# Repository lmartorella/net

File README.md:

# Home

This is a hobbist/educational fulls stack project about Internet of Things (IoT) for DIY enthusiasts. It starts from scratch, using bare microcontrollers (MCU), network, and PC software without any relevant dependency.

The idea is about implementing a lost-cost open-source, open-hardware wired platform for general purpose automation control (for example domotic projects, security, garden automation, etc...). It is designed to connect a whole home and its surroundings.

The core of the project is a tiny MCU board that can embedded in any hardware, even a normal wall switch.

Node-to-node communication happens via common 4-wire or 6-wire low-voltage cables, like KNX, CAN-bus or other commercial systems, using industrial-grade [RS-485](https://en.wikipedia.org/wiki/RS-485) specifications for great scalability. Node-to-master communication is through IP (e.g. ethernet, wifi, etc...) for improved scalability. This allow wireless nodes to be implemented as well. 

What this project is aimed to:
- connect any type of sensor 
- integrate devices that can be interfaced via a MCU
- log data
- implement custom logic to automate tasks
- have a web interface for remote control

The bus structure allow extension with other open standards for IoT.

# The network

The network topology uses two mediums: a custom wired low-voltage bus to allow simple MCUs to be used, and a higher LAN/IP level to aggregate wired sections and server connection.

The wired design is similar to the [KNX](https://en.wikipedia.org/wiki/KNX_(standard)) open standard. However, instead of using proprietary electrical bus drivers, it relies on the broadly available [RS-485](https://en.wikipedia.org/wiki/RS-485) standard (for example, a [Maxim MAX485 IC](https://www.maximintegrated.com/en/products/interface/transceivers/MAX485.html) can be used as a driver).

An industrial-level RS-485 bus can range up to 32 nodes on the same wire and span hundreds of meters, even on electrically noisy environments. See [Maxim Integrated AN](https://www.maximintegrated.com/en/app-notes/index.mvp/id/3884).

Frames are byte-oriented, allowing a common bi-directional [UART](https://en.wikipedia.org/wiki/Universal_asynchronous_receiver-transmitter) to be used. This simplifies the selection of the hardware, since no bit-level CAN-bus or MODBUS logic is required. 

Each wired section needs to contain a *master* node, that allows IP connection to the server through Wi-Fi or Ethernet cables (it needs both UDP and TCP).

The custom protocol built on top is designed to offer features to ease the network installation:
- Auto-discovery for all connected nodes
- Zero-configuration: allow dynamic allocation of nodes via push-button and a PC application
- Fail-over due to bus failures, IP connection failures or node failures.

The byte-level message-based protocol is then shared between wired sections and to increase simplicity and issue analysis.

More details [in this page](doc/protocol.md).

# The microbean (µBean)

The prototyped hardware is a small board (just 30x28mm) built around a cost-effective [Microchip PIC16F1827 MCU](https://www.microchip.com/wwwproducts/en/PIC16F1827), a RS-485 level adapter and a voltage regulator. The board expose almost all MCU lines to the maker, allowing a great amount of free digital and analog I/O pins.

Once the MCU are programmed, the network topology can be easily configured with a PC.

Each physical node exposes one or more applicative drivers, called *sinks*. In this way, a single bean can be programmed to interface more than one device.

More details can be found [here](./src/nodes/doc/microbean.md).

# Some examples

A collection of sample code for beans can be found in the samples folder.

Each sample is documented [here](./samples/beans/README.md).

## Light control

One bean installed in each wall box.
- Common switches will be used as low power digital switch drivers, or push button style
- Touch switches support
- RGB LEDs can be installed in each switch allowing soft tone transitions and night mode
- Power line relays or FET boards in separated junction boxes to control lights
- PWM with zero-cross detection dimmer boards for bulbs that support it
- IR motion/presence sensors support
- Luminance sensors for power saving support

## Intrusion detection and report

- A bean for each IR/motion sensor.
- A bean in junction boxes for window and doors magnetic switch.
- Beans at entrances for RFID or physical keys.
- Real-time notification of unusual activity
- Phone call/SMS/IM alert
- Remote control
- Remote activation/deactivation
- Smartphone control

## Climatization

Beans can be used to interact with existing climatization systems
- Temperature and humidity sensors
- IR emitters for fans and air conditioning units
- Actuator interfacing for motorized window shutters
- Regulation made based on weather forecast services

## Garden irrigation system

- Beans to control electrical valves
- Rain sensors
- Level meter for water tanks
- Relays board for submerged pumps
- Planning made based on weather forecast services

## Power management

- Interfacing with power meters that supports a serial port or a IP protocol.
- Interfacing with solar inverters.
- Wind meters to auto-close awnings.
- Connection with smart meters and devices.

# How to build

The project contains software elements (the .NET server, the node simulators and the control panel UI), hardware (the microbean) and the firmware for these nodes.

It is however possible to run the system with a software-only environment, using the node simulators to have a try.

## The server

The server code is a C# command-line process. It doesn't have any 3rd party dependency other than the .NET Framework, and it could be easily ported to [.NET Core](https://dotnet.microsoft.com/download).

However, currently it requires [Visual Studio](https://visualstudio.microsoft.com/) and [.NET Framework 4.x](https://dotnet.microsoft.com/download).

The project is splitted between the core part and the samples dlls, that are loaded automatically at startup via a plug-in load system, allowing modular architecture.

In addition, a WPF application is generated as a administrative interface (to visualize and set-up the network hierarchy) and to allow simulation of node logic and his sinks.

See [here](src/server/README.md) for more information.

## The master node

A master node is required to translate the IP connection from the server to the wired sections.

Custom hardware can be used there, but the simplest solution is perhaps to use an Arduino or a [Raspberry Pi Zero W](https://www.raspberrypi.org/products/raspberry-pi-zero-w/): something that can drive a bidirectional serial port and that can be connected to the LAN.

In this project you will found two implementations:
- for Raspberry (Raspbian) 
- for Microchip MCU with Ethernet support (e.g. PIC18F87). The [Microchip MPLAB X IDE](https://www.microchip.com/mplab/mplab-x-ide) with [XC8 compiler](https://www.microchip.com/mplab/compilers) is required in this case.

See [here](src/nodes/README.md) for more information.

## The wired node

You will find the schematics and the Microchip firmware to implement a wired node. Different ranges of MCU can be used, since the code and data requirements are quite limited.

The [Microchip MPLAB X IDE](https://www.microchip.com/mplab/mplab-x-ide) with [XC8 compiler](https://www.microchip.com/mplab/compilers) is required to compile the firmware and the samples.

See [here](src/nodes/README.md) for more information.

## The web server

A minimalistic web-server implementation is presented to allow remote access to the applications exposed by the server.

See [here](src/web/README.md) for more information.

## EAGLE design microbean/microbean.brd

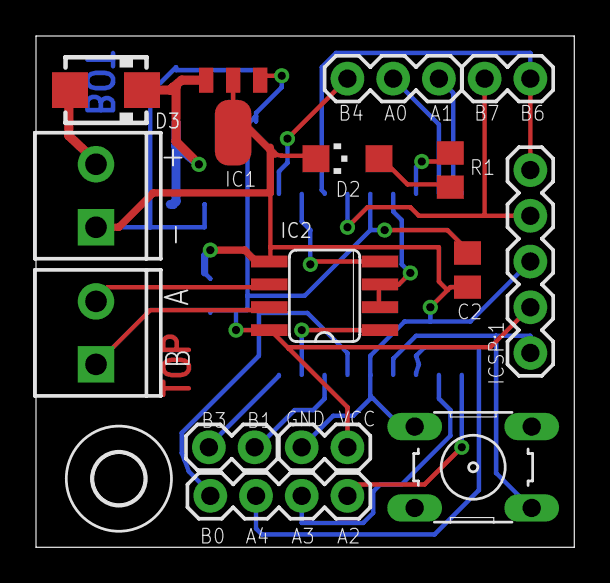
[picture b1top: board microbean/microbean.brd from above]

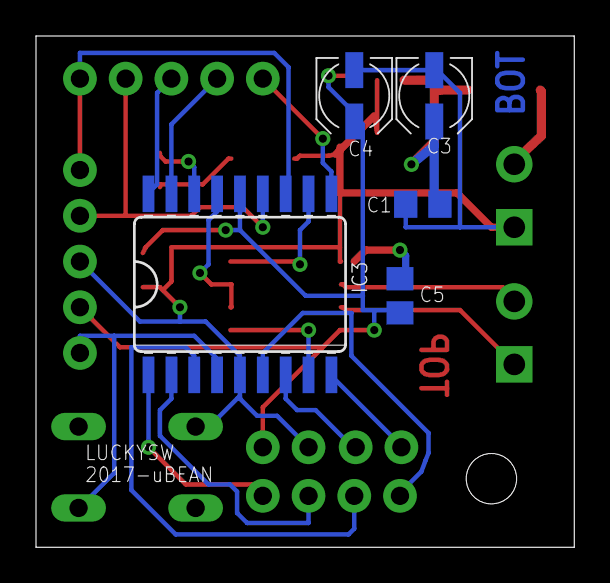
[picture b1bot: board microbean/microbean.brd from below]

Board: 2 copper layers, 29.9 x 28.4 mm, 21 parts (5 on the bottom side), 23 nets.

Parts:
C1, C2, C5: 100n; C0805
C3, C4: 10u; UD-4X5,8_NICHICON
D2: LED1206; CHIPLED_1206
D3: S1A; SMA
IC1: L78L33/L78L05; SOT89
IC2: ST485/ST3485; SO08
IC3: PIC16F1827SO18; SO18W
ICSP: ICSP-HEADER-5; 1X05
J1, J2: SCREWTERMINAL-3.5MM-2
J3: 1X03
J4: 1X04
J5, J6, J7: 1X02
R1: 560; R0805
U$2: PUSH-BUTTON; MICRO-SWITCH
U$4: 2,8

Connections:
A: IC2.6, J2.2
B: IC2.7, J2.1
GND: C1.2, C2.2, C3.-, C4.-, C5.2, D2.C, IC1.2, IC1.2@1, IC2.5, IC3.5, ICSP.3, J1.1, J5.2, U$2.1
MCLR: IC3.4, ICSP.1, U$2.4
unnamed: D3.A, J1.2
unnamed: C1.1, C3.+, D3.C, IC1.3
unnamed: D2.A, R1.2
RA0: IC3.17, J3.2
RA1: IC3.18, J3.3
RA2: IC3.1, J4.1
RA3: IC3.2, J4.2
RA4: IC3.3, J4.3
RA6: IC2.2, IC2.3, IC3.15
RA7: IC3.16, R1.1
RB0: IC3.6, J4.4
RB1: IC3.7, J7.2
RB2: IC2.1, IC3.8
RB3: IC3.9, J7.1
RB4: IC3.10, J3.1
RB5: IC2.4, IC3.11
RB6: IC3.12, ICSP.5, J6.2
RB7: IC3.13, ICSP.4, J6.1
VCC: C2.1, C4.+, C5.1, IC1.1, IC2.8, IC3.14, ICSP.2, J5.1

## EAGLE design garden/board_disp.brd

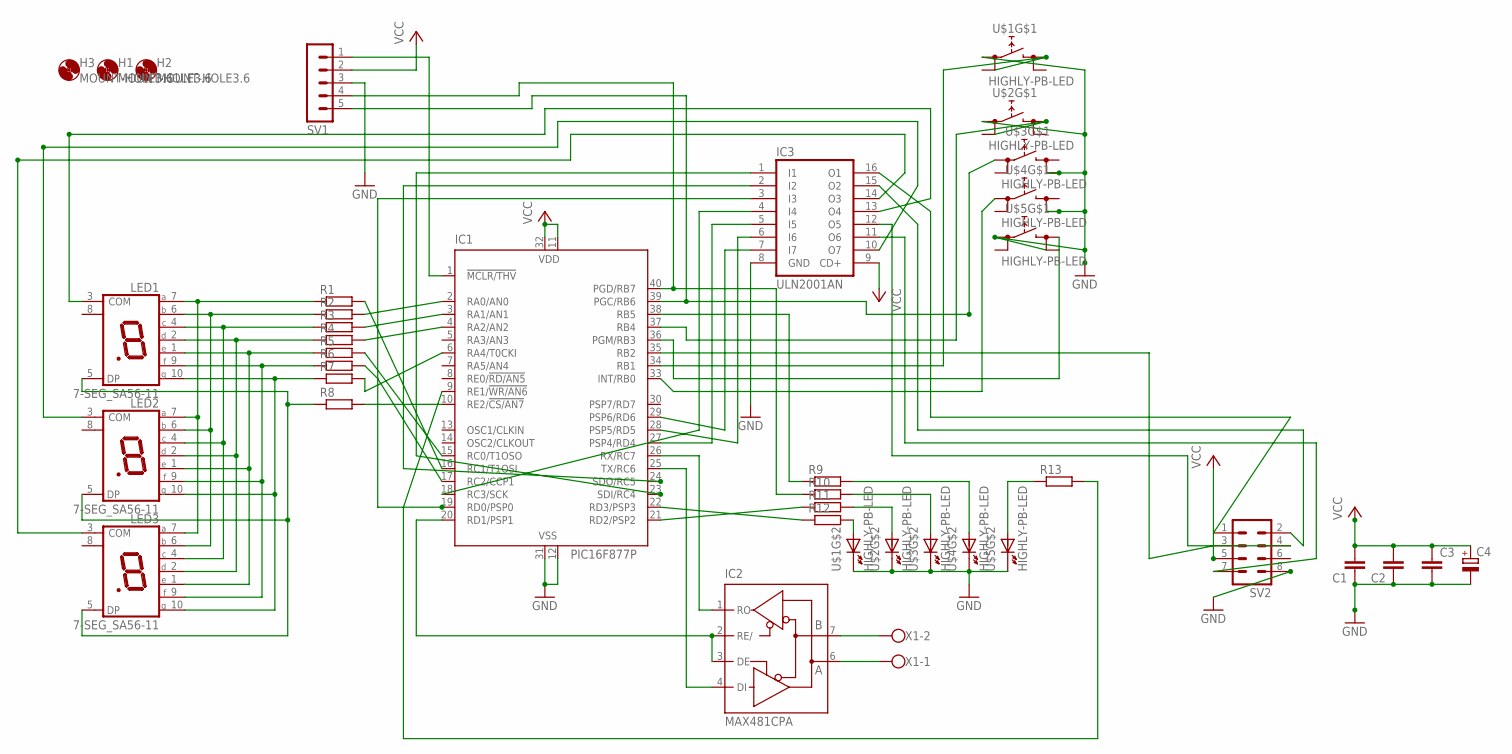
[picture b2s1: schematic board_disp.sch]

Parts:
C1, C2, C3: C-EU025_050-025X075; C025_050-025X075
C4: CPOL-EUE3.5-8; E3,5-8
H1, H2, H3: MOUNT-HOLE3.6; 3,6
IC1: PIC16F877P; DIL40
IC2: MAX481CPA; DIL08
IC3: ULN2001AN; DIL16
LED1, LED2, LED3: 7-SEG_SA56-11; SA56-11
R1, R2, R3, R4, R5, R6, R7, R8, R9, R10, R11, R12, R13: R-EU_0207/10; 0207/10
SV1: MA05-1
SV2: MA04-2
U$1, U$2, U$3, U$4, U$5: HIGHLY-PB-LED; HIGHLY-PUSHBUTTON
X1: PASSO3

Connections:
GND: C1.1, C2.1, C3.2, C4.-, IC1.12 (VSS), IC1.31 (VSS), IC2.5 (GND), IC3.8 (GND), SV1.3, SV2.8, U$1.1A (0), U$1.K, U$2.1A (0), U$2.K, U$3.2B (1), U$3.K, U$4.2B (1), U$4.K, U$5.1A (0), U$5.K
unnamed: IC1.36 (PGM/RB3), U$5.2A (1)
unnamed: IC1.33 (INT/RB0), U$4.1A (0)
unnamed: IC1.39 (PGC/RB6), SV1.5, U$3.1A (0)
unnamed: IC1.37 (RB4), U$2.2A (1)
unnamed: IC1.34 (RB1), U$1.2A (1)
unnamed: IC1.6 (RA4/T0CKI), R7.2
unnamed: LED1.5 (DP), LED2.5 (DP), LED3.5 (DP), R8.1
unnamed: IC1.10 (RE2/!CS/AN7), R8.2
unnamed: IC1.22 (RD3/PSP3), R12.1
unnamed: R12.2, U$1.A
unnamed: R11.2, U$2.A
unnamed: R10.2, U$3.A
unnamed: R9.2, U$4.A
unnamed: IC1.16 (RC1/T1OSI), R1.2
unnamed: LED1.7 (A), LED2.7 (A), LED3.7 (A), R1.1
unnamed: LED1.6 (B), LED2.6 (B), LED3.6 (B), R2.1
unnamed: LED1.4 (C), LED2.4 (C), LED3.4 (C), R3.1
unnamed: LED1.2 (D), LED2.2 (D), LED3.2 (D), R4.1
unnamed: LED1.1 (E), LED2.1 (E), LED3.1 (E), R5.1
unnamed: LED1.9 (F), LED2.9 (F), LED3.9 (F), R6.1
unnamed: LED1.10 (G), LED2.10 (G), LED3.10 (G), R7.1
unnamed: IC1.21 (RD2/PSP2), R11.1
unnamed: IC1.18 (RC3/SCK), IC3.4 (I4)
unnamed: IC1.27 (PSP4/RD4), IC3.5 (I5)
unnamed: IC1.17 (RC2/CCP1), R6.2
unnamed: IC1.15 (RC0/T1OSO), R5.2
unnamed: IC1.4 (RA2/AN2), R4.2
unnamed: IC1.3 (RA1/AN1), R3.2
unnamed: IC1.2 (RA0/AN0), R2.2
unnamed: IC1.38 (RB5), R9.1
unnamed: IC2.7 (B), X1.2
unnamed: IC2.6 (A), X1.1
unnamed: IC1.23 (SDI/RC4), IC3.1 (I1)
unnamed: IC1.24 (SDO/RC5), IC3.2 (I2)
unnamed: IC1.19 (RD0/PSP0), IC3.3 (I3)
unnamed: IC3.13 (O4), LED1.3 (COM)
unnamed: IC3.10 (O7), LED2.3 (COM)
unnamed: IC3.14 (O3), LED3.3 (COM)
unnamed: IC1.35 (RB2), SV2.3
unnamed: IC1.29 (PSP6/RD6), IC3.7 (I7)
unnamed: IC1.28 (PSP5/RD5), IC3.6 (I6)
unnamed: IC1.26 (RX/RC7), IC2.1 (RO)
unnamed: IC1.25 (TX/RC6), IC2.4 (DI)
unnamed: IC1.20 (RD1/PSP1), IC2.2 (RE/), IC2.3 (DE)
unnamed: IC1.40 (PGD/RB7), R10.1, SV1.4
unnamed: IC1.1 (!MCLR/THV), SV1.1
unnamed: IC3.16 (O1), SV2.1
unnamed: IC3.15 (O2), SV2.2
unnamed: IC3.11 (O6), SV2.7
unnamed: IC3.12 (O5), SV2.4
unnamed: R13.1, U$5.A
unnamed: IC1.9 (RE1/!WR/AN6), R13.2
VCC: C1.2, C2.2, C3.1, C4.+, IC1.11 (VDD), IC1.32 (VDD), IC2.8 (VCC), IC3.9 (CD+), SV1.2, SV2.5

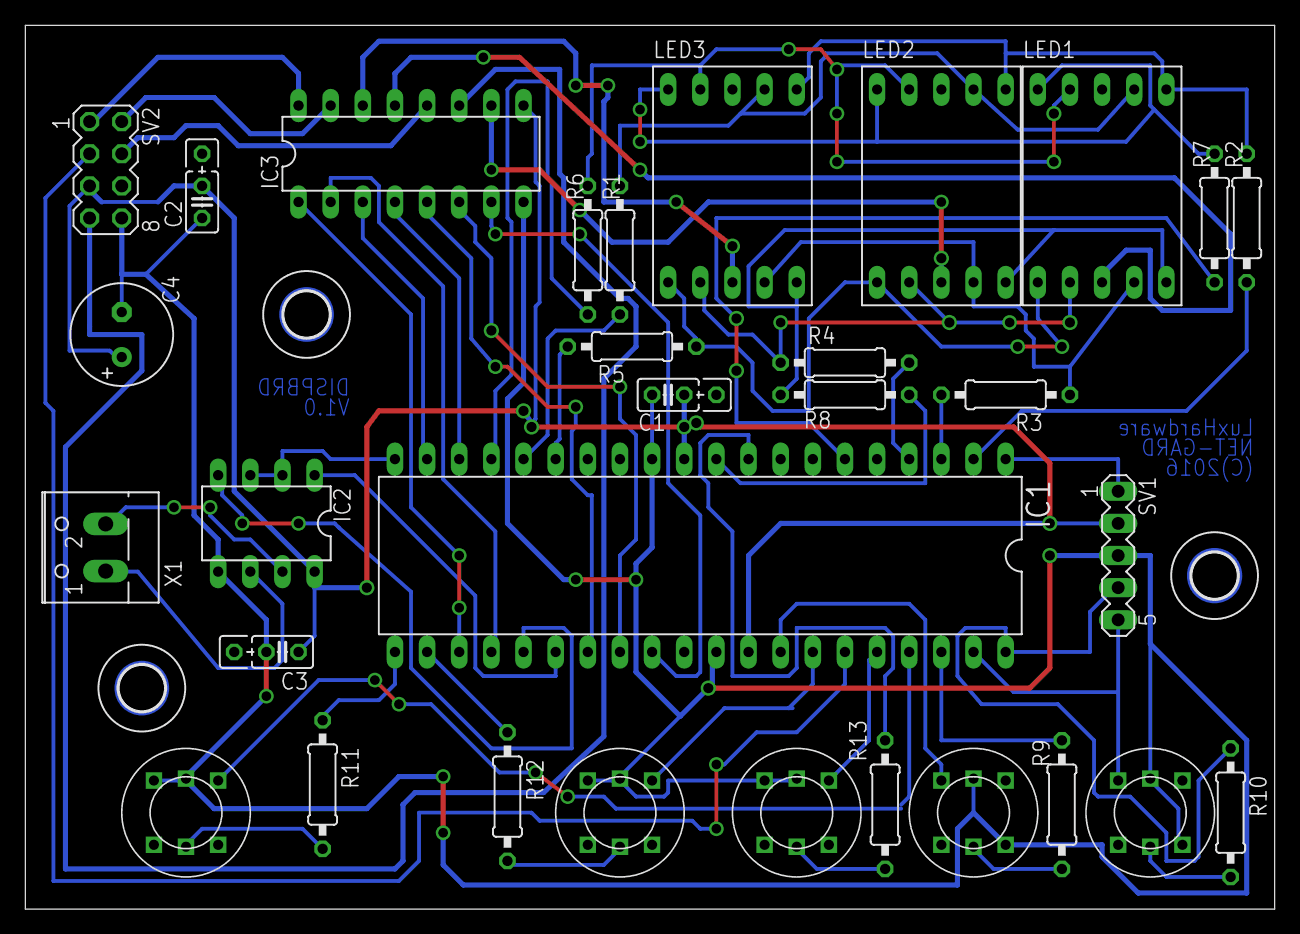
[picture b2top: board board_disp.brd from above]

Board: 2 copper layers, 98.7 x 69.8 mm, 34 parts (0 on the bottom side), 54 nets.

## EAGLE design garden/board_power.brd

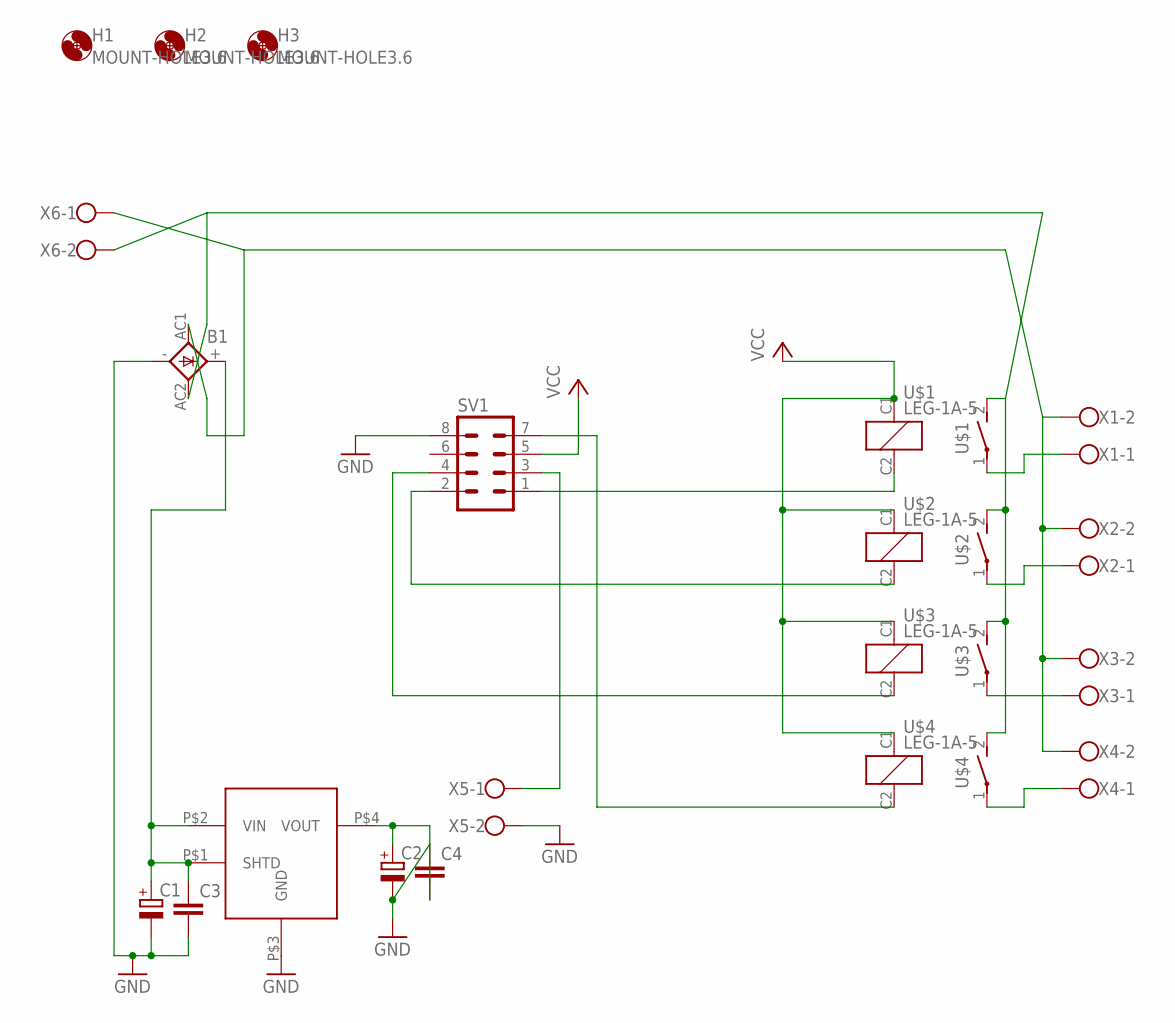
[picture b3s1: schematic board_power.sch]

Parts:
B1: KBK10A
C1, C2: CPOL-EUE5-4; E5-4
C3, C4: C-EU025_050-025X075; C025_050-025X075
H1, H2, H3: MOUNT-HOLE3.6; 3,6
SV1: MA04-2
U$1, U$2, U$3, U$4: LEG-1A-5; LEG
U$5: POLOLU-2098
X1, X2, X3, X4, X5, X6: PASSO3

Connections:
GND: B1.-, C1.-, C2.-, C3.2, C4.1, SV1.8, U$5.P$3 (GND), X5.2
unnamed: SV1.1, U$1.C2 (2)
unnamed: SV1.2, U$2.C2 (2)
unnamed: SV1.4, U$3.C2 (2)
unnamed: SV1.7, U$4.C2 (2)
unnamed: SV1.3, X5.1
unnamed: B1.AC2, U$1.2 (S), U$2.2 (S), U$3.2 (S), U$4.2 (S), X6.2
unnamed: B1.AC1, X1.2, X2.2, X3.2, X4.2, X6.1
unnamed: U$1.1, X1.1
unnamed: U$2.1, X2.1
unnamed: U$3.1, X3.1
unnamed: U$4.1, X4.1
unnamed: B1.+, C1.+, C3.1, U$5.P$1 (SHTD), U$5.P$2 (VIN)
unnamed: C2.+, C4.2, U$5.P$4 (VOUT)
VCC: SV1.5, U$1.C1 (1), U$2.C1 (1), U$3.C1 (1), U$4.C1 (1)

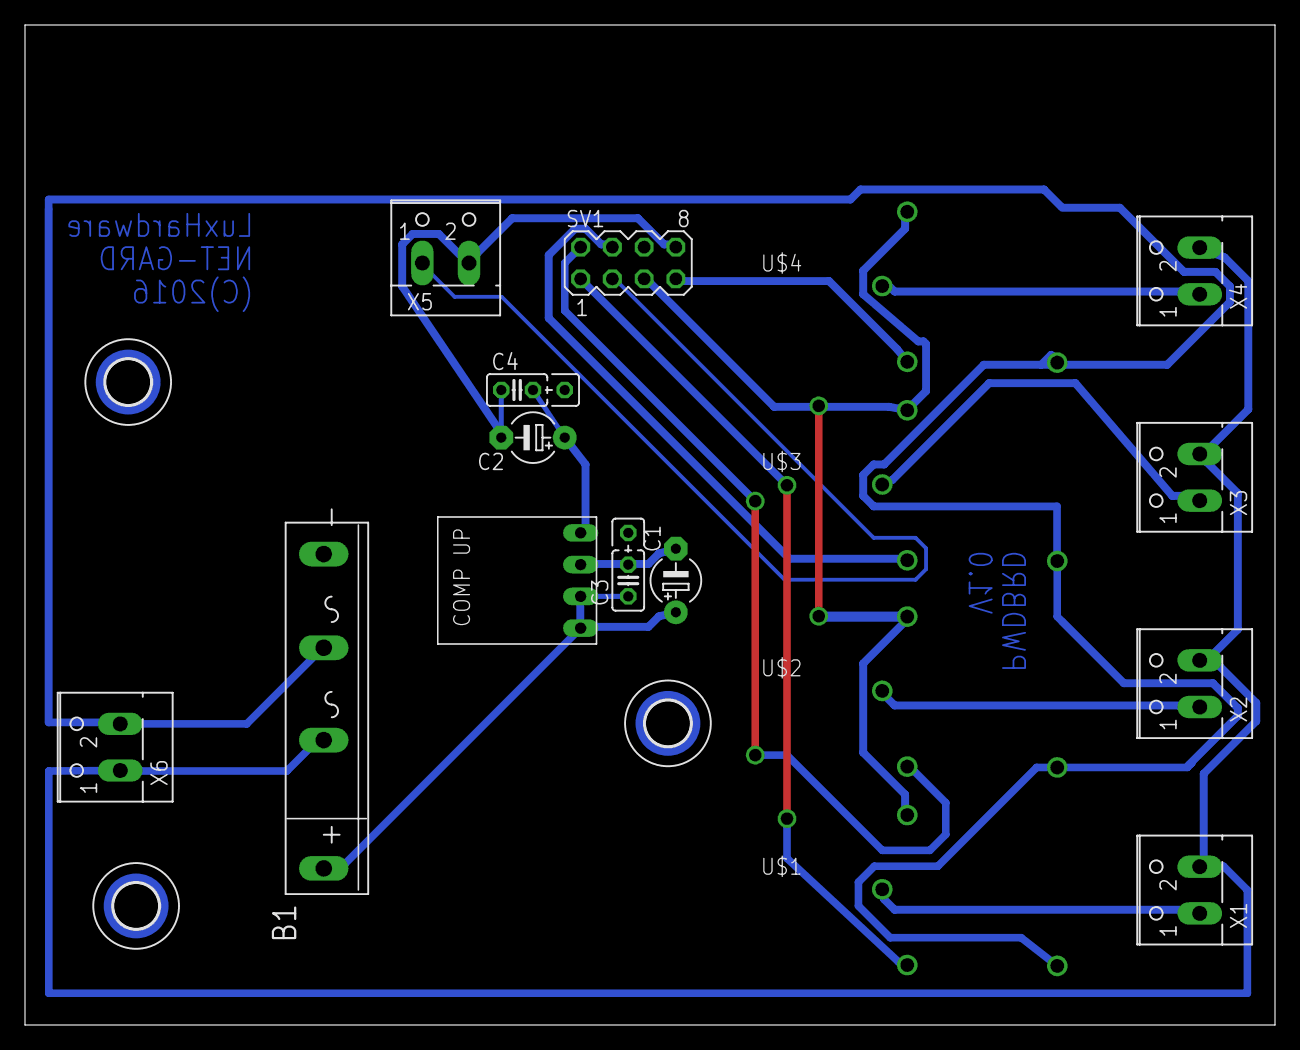
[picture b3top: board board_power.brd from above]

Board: 2 copper layers, 100.0 x 80.0 mm, 20 parts (0 on the bottom side), 15 nets.

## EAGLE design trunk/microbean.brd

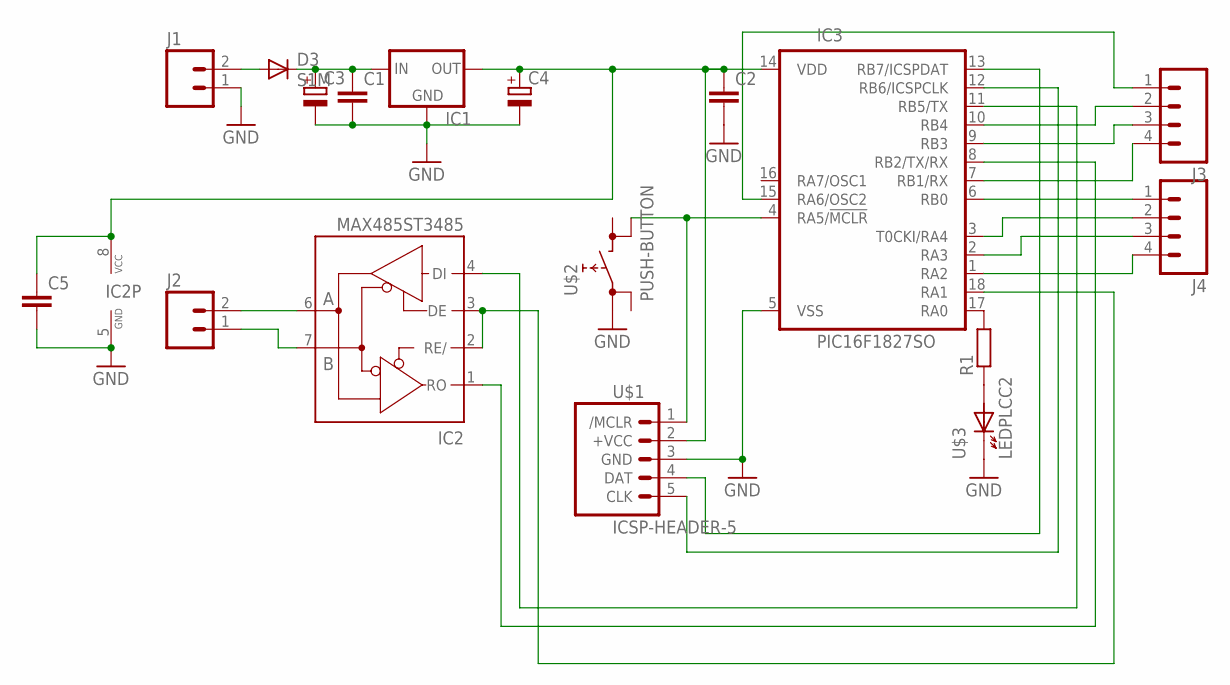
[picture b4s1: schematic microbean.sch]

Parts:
C1, C2, C5: C-EUC0805; C0805
C3, C4: CPOL-EUE2-4; E2-4
D3: S1M; SMA
IC1: 78LXXSOT89; SOT89
IC2: MAX485ST3485; SO08
IC3: PIC16F1827SO; SO-18W
J1, J2: M02-SCREW-3.5MM3.5MM; SCREWTERMINAL-3.5MM-2
J3, J4: M04; 1X04
R1: R-EU_R0805; R0805
U$1: ICSP-HEADER-5; 1X05
U$2: PUSH-BUTTON; MICRO-SWITCH
U$3: LEDPLCC2; P-LCC-2

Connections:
GND: C1.2, C2.2, C3.-, C4.-, C5.2, IC1.2 (GND), IC2.5 (GND), IC3.5 (VSS), J1.1, U$1.3 (GND), U$2.1 (0), U$3.C (K)
unnamed: D3.A, J1.2
unnamed: C1.1, C3.+, D3.C, IC1.3 (IN)
unnamed: IC2.7 (B), J2.1
unnamed: IC2.6 (A), J2.2
unnamed: IC3.4 (RA5/!MCLR), U$1.1 (/MCLR), U$2.4 (1)
unnamed: IC3.13 (RB7/ICSPDAT), U$1.4 (DAT)
unnamed: IC3.12 (RB6/ICSPCLK), U$1.5 (CLK)
unnamed: IC3.17 (RA0), R1.2
unnamed: R1.1, U$3.A
unnamed: IC2.4 (DI), IC3.11 (RB5/TX)
unnamed: IC2.1 (RO), IC3.8 (RB2/TX/RX)
unnamed: C2.1, C4.+, C5.1, IC1.1 (OUT), IC2.8 (VCC), IC3.14 (VDD), U$1.2 (+VCC)
unnamed: IC3.1 (RA2), J4.4
unnamed: IC3.2 (RA3), J4.3
unnamed: IC3.3 (T0CKI/RA4), J4.2
unnamed: IC3.6 (RB0), J4.1
unnamed: IC3.7 (RB1/RX), J3.4
unnamed: IC3.9 (RB3), J3.3
unnamed: IC3.10 (RB4), J3.2
unnamed: IC3.15 (RA6/OSC2), J3.1
unnamed: IC2.2 (RE/), IC2.3 (DE), IC3.18 (RA1)

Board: 2 copper layers, 17 parts (1 on the bottom side), 22 nets, no tracks yet.

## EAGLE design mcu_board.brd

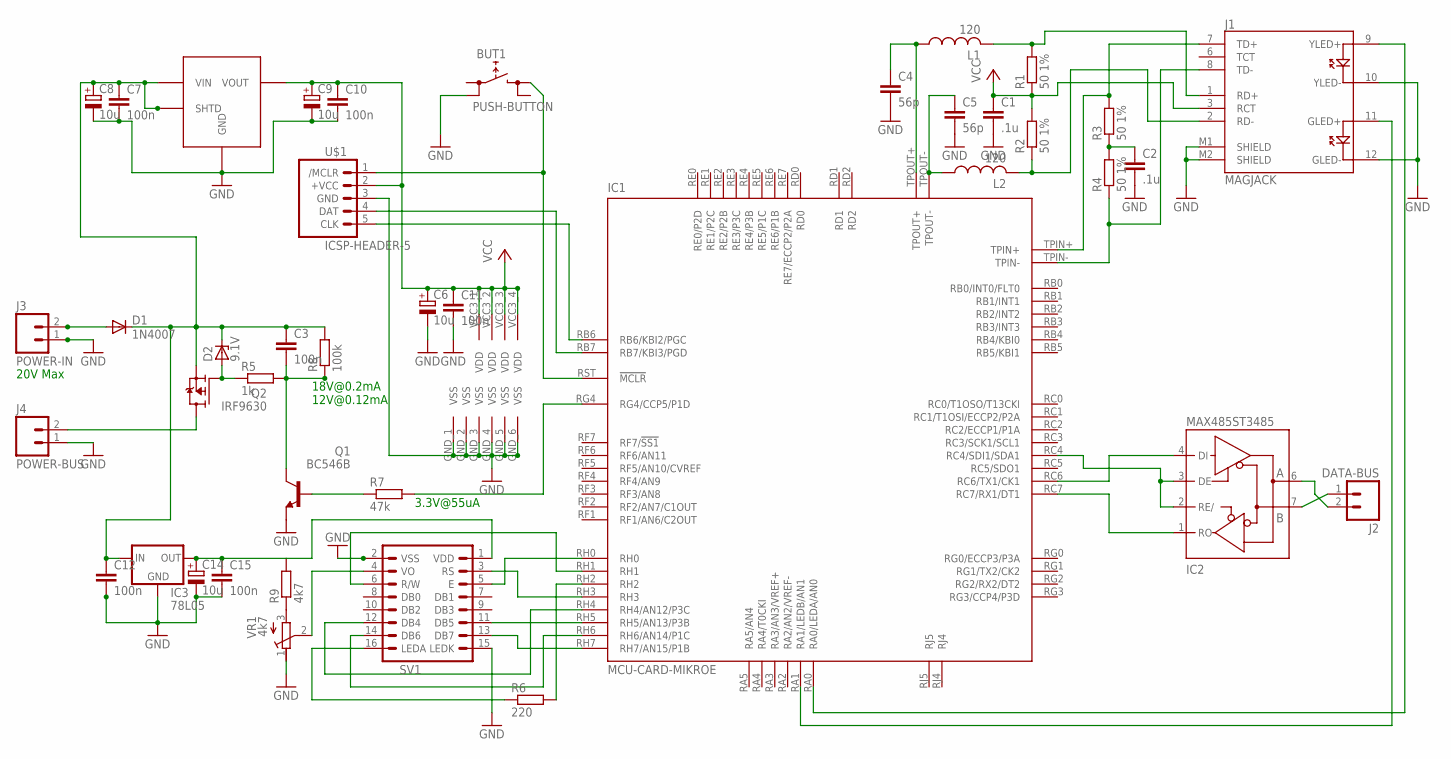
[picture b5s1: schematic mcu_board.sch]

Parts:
BUT1: PUSH-BUTTON; MICRO-SWITCH
C1, C2: .1u; C050-025X075
C3, C7, C10, C11, C12, C15: 100n; C050-025X075
C4, C5: 56p; C0805
C6: 10u; E2,5-6
C8, C9, C14: 10u; E2,5-7
D1: 1N4007; DO41-10
D2: 9.1V; D-5
IC1: MCU-CARD-MIKROE; LV18F
IC2: MAX485ST3485; SO08
IC3: 78L05; 78LXX
J1: MAGJACK
J2: DATA-BUS; SCREWTERMINAL-3.5MM-2
J3: POWER-IN; SCREWTERMINAL-3.5MM-2
J4: POWER-BUS; SCREWTERMINAL-3.5MM-2
L1, L2: 120; R0603
Q1: BC546B; TO92-
Q2: IRF9630; TO220V
R1, R2, R3, R4: 50 1%; 0207/10
R5: 1k; 0207/10
R6: 220; 0207/10
R7: 47k; 0207/10
R8: 100k; 0207/10
R9: 4k7; 0207/10
SV1: WM-C2002M-DISP; MA08-2
U$1: ICSP-HEADER-5; 1X05
U$3: POLOLU-2098; POLOLU-10-13
VR1: 4k7; V_TRIMMER

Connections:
GND: BUT1.2 (0), C1.2, C2.2, C4.2, C5.2, C6.-, C7.2, C8.-, C9.-, C10.2, C11.2, C12.2, C14.-, C15.2, IC1.GND_1 (VSS), IC1.GND_2 (VSS), IC1.GND_3 (VSS), IC1.GND_4 (VSS), IC1.GND_5 (VSS), IC1.GND_6 (VSS), IC2.5 (GND), IC3.GND, J1.10 (YLED-), J1.12 (GLED-), J1.M1 (SHIELD), J1.M2 (SHIELD), J3.1, J4.1, Q1.1 (E), SV1.2 (VSS), SV1.15 (LEDK), U$1.3 (GND), U$3.P$3 (GND), VR1.1 (A)
unnamed: C4.1, IC1.TPOUT+, L1.1
unnamed: C2.1, R3.1, R4.2
unnamed: J1.1 (RD+), L1.2, R1.2
unnamed: J1.2 (RD-), L2.2, R2.1
unnamed: IC1.TPIN+, J1.7 (TD+), R3.2
unnamed: IC1.TPIN-, J1.8 (TD-), R4.1
unnamed: C5.1, IC1.TPOUT-, L2.1
unnamed: IC1.RC7 (RC7/RX1/DT1), IC2.1 (RO)
unnamed: IC1.RA0 (RA0/LEDA/AN0), J1.9 (YLED+)
unnamed: IC1.RA1 (RA1/LEDB/AN1), J1.11 (GLED+)
unnamed: IC1.RC6 (RC6/TX1/CK1), IC2.4 (DI)
unnamed: IC1.RC4 (RC4/SDI1/SDA1), IC2.2 (RE/), IC2.3 (DE)
unnamed: BUT1.3 (1), IC1.RST (!MCLR), U$1.1 (/MCLR)
unnamed: IC1.RB6 (RB6/KBI2/PGC), U$1.5 (CLK)
unnamed: IC1.RB7 (RB7/KBI3/PGD), U$1.4 (DAT)
unnamed: IC1.RH0, SV1.5 (E)
unnamed: IC1.RH1, SV1.6 (R/W)
unnamed: IC2.7 (B), J2.1
unnamed: IC1.RH3, SV1.3 (RS)
unnamed: IC1.RH4 (RH4/AN12/P3C), SV1.12 (DB4)
unnamed: IC1.RH5 (RH5/AN13/P3B), SV1.11 (DB5)
unnamed: IC1.RH6 (RH6/AN14/P1C), SV1.14 (DB6)
unnamed: IC1.RH7 (RH7/AN15/P1B), SV1.13 (DB7)
unnamed: IC2.6 (A), J2.2
unnamed: D1.A, J3.2
unnamed: SV1.4 (VO), VR1.2 (S)
unnamed: J4.2, Q2.2 (D)
unnamed: IC1.RG4 (RG4/CCP5/P1D), R7.2
unnamed: D2.A, Q2.1 (G), R5.1
unnamed: R6.1, SV1.16 (LEDA)
unnamed: IC1.RH2, R6.2
unnamed: C3.2, Q1.3 (C), R5.2, R8.1
unnamed: Q1.2 (B), R7.1
unnamed: R9.1, VR1.3 (E)
VCC: C1.1, C6.+, C9.+, C10.1, C11.1, IC1.VCC3_1 (VDD), IC1.VCC3_2 (VDD), IC1.VCC3_3 (VDD), IC1.VCC3_4 (VDD), IC2.8 (VCC), J1.3 (RCT), R1.1, R2.2, U$1.2 (+VCC), U$3.P$4 (VOUT)
VCC5: C14.+, C15.1, IC3.OUT, R9.2, SV1.1 (VDD)
VIN: C3.1, C7.1, C8.+, C12.1, D1.C, D2.C, IC3.IN, Q2.3 (S), R8.2, U$3.P$1 (SHTD), U$3.P$2 (VIN)

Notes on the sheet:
18V@0.2mA 12V@0.12mA
3.3V@55uA
20V Max

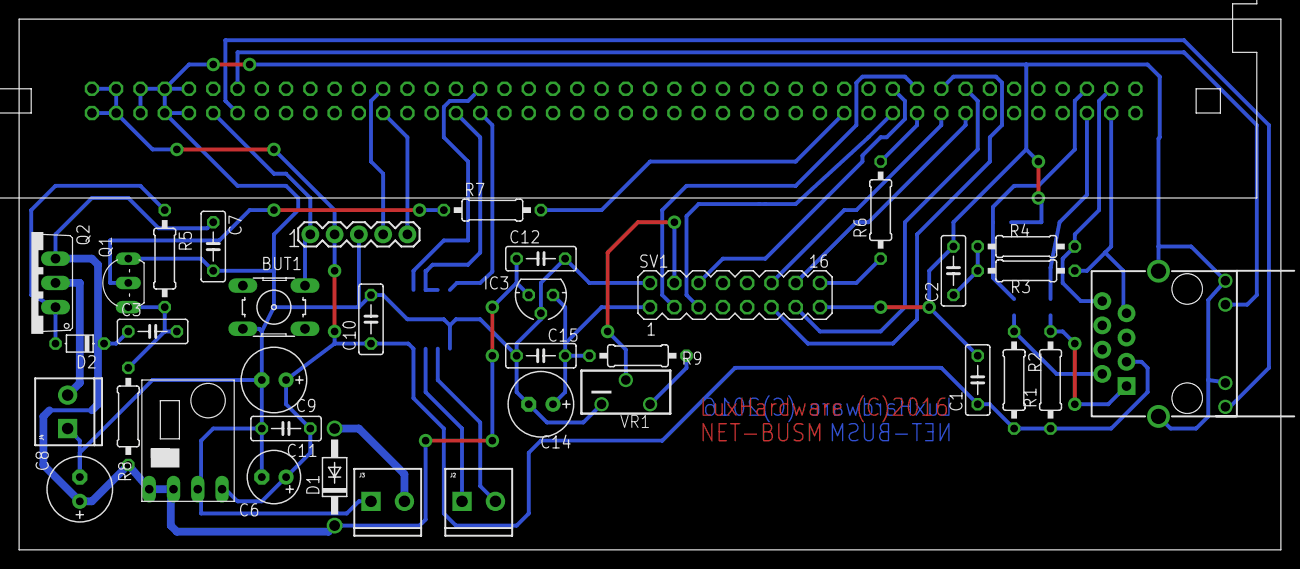
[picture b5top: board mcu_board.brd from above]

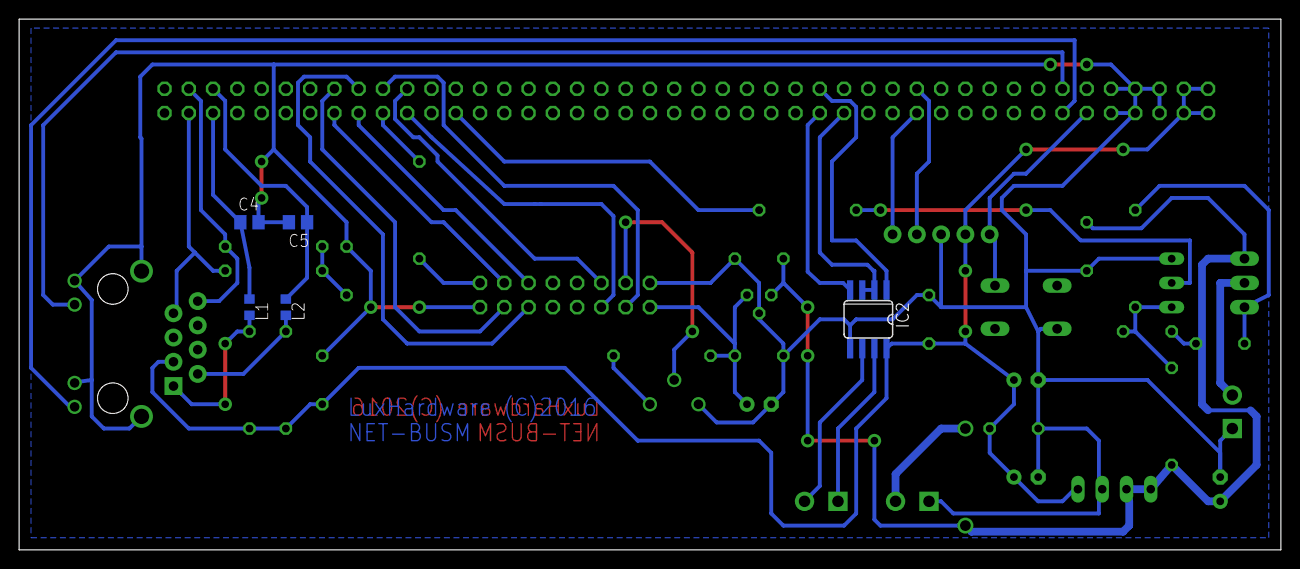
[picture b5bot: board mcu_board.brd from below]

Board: 2 copper layers, 132.1 x 55.5 mm, 41 parts (5 on the bottom side), 38 nets.

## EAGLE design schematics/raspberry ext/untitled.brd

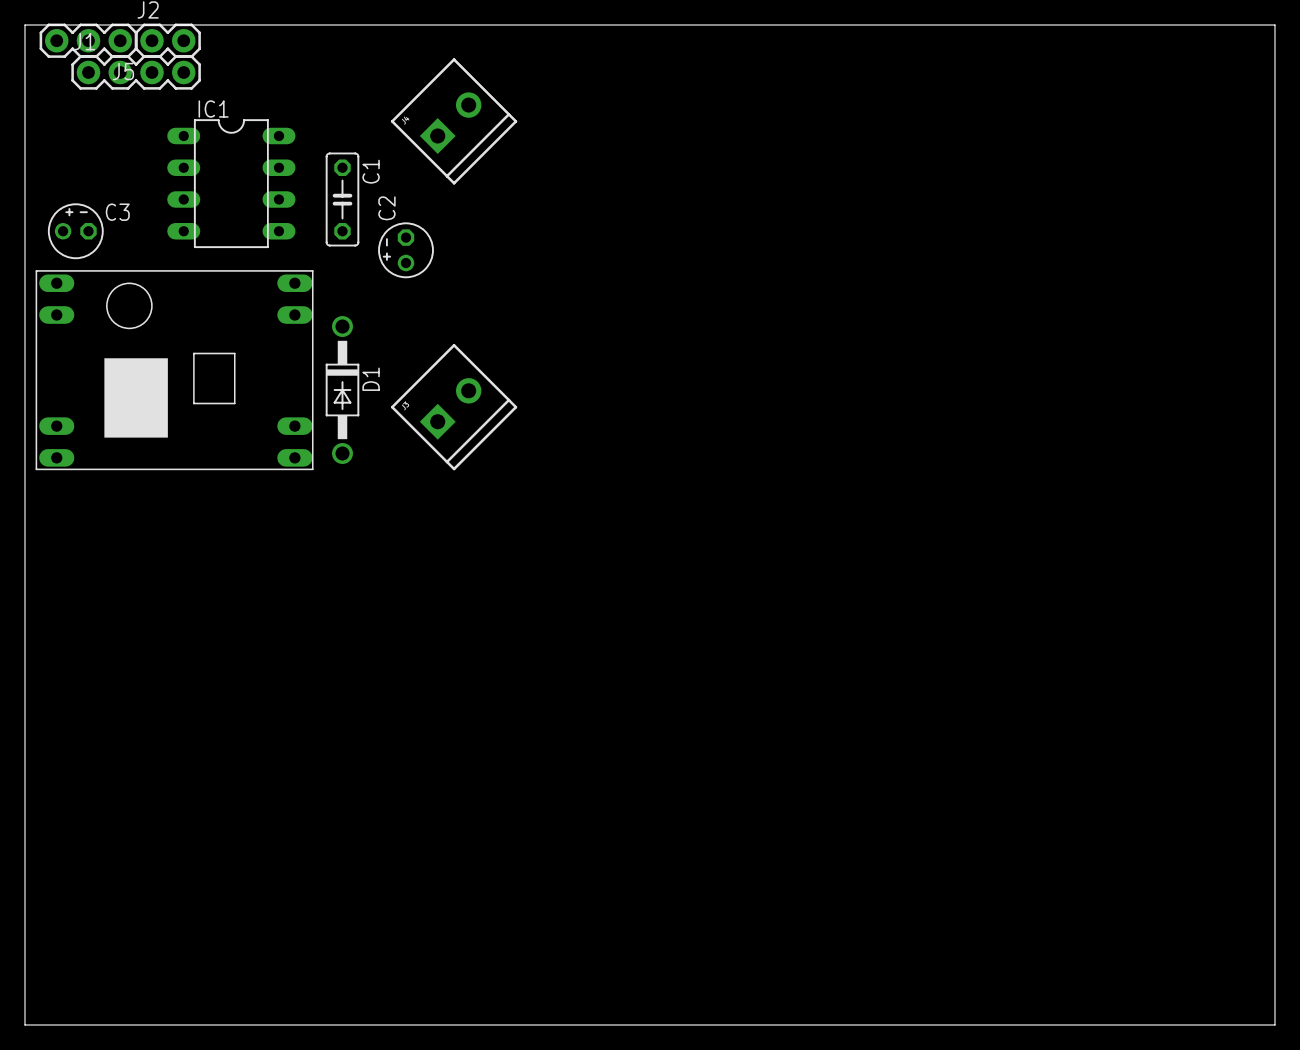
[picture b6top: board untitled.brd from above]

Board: 2 copper layers, 100.0 x 80.0 mm, 11 parts (0 on the bottom side), 10 nets, no tracks yet.

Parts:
C1: C050-025X075
C2, C3: E2-4
D1: 1N4007; DO41-10
IC1: MAX485; DIL08
J1: 1X04
J2: 1X02
J3, J4: SCREWTERMINAL-3.5MM-2
J5: 1X03
U$1: DSUN-MP1584

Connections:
3.3V: C1.1, IC1.8, J1.4
5V: C3.+, J2.1, J2.2, U$1.OUT1
A: IC1.6, J4.1
B: IC1.7, J4.2
EN: IC1.2, IC1.3, J1.3
GND: C1.2, C2.-, C3.-, IC1.5, J3.2, J5.1, U$1.GND1
unnamed: D1.A, J3.1
unnamed: C2.+, D1.C, U$1.IN1
RX: IC1.1, J5.3
TX: IC1.4, J5.2

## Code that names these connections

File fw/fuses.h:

#ifndef _FUSES_INCLUDE_
#define _FUSES_INCLUDE_

#include <p18f87j60.h>
#include "utilities.h"

// ******* 
// DISPLAY
// ******* 
#define CM1602_PORT 		PORTE
#define CM1602_TRIS 		TRISE
#define CM1602_PORTBITS		PORTEbits
#define CM1602_IF_MODE 		4
#define CM1602_IF_NIBBLE 	'high'
#define CM1602_IF_BIT_RW 	PORTEbits.RE2
#define CM1602_IF_BIT_RS 	PORTEbits.RE0
#define CM1602_IF_BIT_EN 	PORTEbits.RE3
#define CM1602_LINE_COUNT 	2
#define CM1602_FONT_HEIGHT 	7

// ******* 
// MEMORY
// ******* 
#define MEM_PORT	 PORTC
#define MEM_PORTBITS PORTCbits
#define MEM_TRISBITS TRISCbits
#define MEM_BANK0_CS RC6
#define MEM_BANK1_CS RC2
#define MEM_BANK2_CS RC7
#define MEM_BANK3_CS RC1

// ******* 
// MP3
// ******* 
#define VS1011_PORT  	PORTB
#define VS1011_PORTBITS PORTBbits
#define VS1011_TRISBITS TRISBbits
#define VS1011_RESET 	RB4
#define VS1011_DREQ  	RB5
#define VS1011_SDATA 	RB2
#define VS1011_DCLK  	RB3
#define VS1011_BSYNC 	RB0
#define VS1011_CS	 	RB1


#endif

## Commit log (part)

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2019-04-23 - Added support for puase
2019-04-23 - Fixed build
2019-04-23 Merged revision(s) 762-767 from netServer/branches/garden: - Implemented new combined zones firmware, protocol and csv/json support (no UI so far)
2019-04-23 - Fixes
2019-04-23 - Changed timeout to fix several zombie
2019-04-23 - Trying to fix infamous csv backup bug
2019-04-23 - Migrated to SPA
2019-04-23 Merged revision(s) 781 from netServer/trunk: - Migrated to SPA ........
2019-04-23 WIP temp module in microbean
2019-04-23 - Merged digio memssage refactoring - TODO DIAR -> event -> DIOR in sync breaks loop
2019-04-23 - Updated fw too with new DIGIO protocol
2019-04-23 - Missing file
2019-04-23 - Fixed DIOR in mock UI and DIAR in SDK
2019-04-23 - Fixed temperature sink mock - Fixed checksum calculation of DHT11 - Added mail in case of DB rotation error, now that is fixed
2019-04-23 - Added support for cycles in garden (multiple zones at the same time)
2019-04-23 - Removed temp
2019-04-23 Adding LICENSE
2019-04-23 - Moved web credentials on setting file
2019-04-23 - Removed old prototypes
2019-04-23 - Added email configuration from file
2019-04-23 - Restructuring folders to split app from lib
2019-04-24 Started documenting API
2019-04-24 Common refactroing done
2019-04-24 Refactored MockUI
2019-04-24 Finished assembly rework of all projects
2019-04-24 Refactored done and working
2019-04-27 WIP spit of mock UI in sample/core, and merge with admin ui
2019-05-01 - WUIP refactoring
2019-05-11 - Refactored type managers and removed device type protocol between Admin and Server
2019-05-12 Finished refactoring registrar and mock UI dll loading
2019-05-12 Fixed slave UI relationship and persistence
2019-05-15 - Removed sink tabs without UI - Added some inline doc on classes - Code cleanup
2019-05-17 - Documenting
2019-07-03 - Added doc for ubean - Documenting
2019-07-03 - Removed old tests, start folder refactoring
2019-07-03 - Folder refactoring
2019-07-03 Compiles the microbean
2019-07-03 - Renamed sample project
2019-07-03 - Fixed NET MCU - Project cleanup
2019-10-03 - Added doc
2019-10-12 - Code fix and documentation
2019-11-03 - Implemented digital input with last event table (for high resolution event log) - Not tested yet
2020-03-22 - Removed support for external trigger - Added support for global Power relais for better power management
2020-03-23 - Added digital input simulator and tester device
2020-03-23 - Fixed serialization of JSON - Added node removal from simulator UI - Fixed UT
2020-03-23 - Implemented flow reading from bus
2020-03-24 - Fixed raspberry netmaster build
2020-03-25 - Fixed digio hw and c# sink driver
2020-03-26 - Added debounce to digital input, at 0.1s (for normal switches and relais)
2020-03-29 - Fixed management of bean MCLR for idx update - Added persistence log for raspberry - Fixed server exception in case of stream dispose
2020-04-04 - Added statistics log in raspberry master nodes to analyze disconnection loop - Fixed TCP management in server to avoid loop of connections and disconnections, and refactor code to improve readabili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
2020-04-04 - Added pump logger - Refactored the big Garden device file in sub classes
2020-04-05 - I18N of the web GUI
2020-04-07 - Protocol webserver/server reworked - .NET message separation samples/core
2020-04-07 - Completed loaded async reaction - Fixed daylight management after restart
2020-04-07 - Better mail report (text) - Added Night Mode switch in the simulator - Added protocol debug
2020-04-13 Merged bean-dip
2020-04-13 - Aligned top symbols
2020-04-13 Refolder
2020-04-13 - refoldered
2020-04-13 - WIP microbean for professional printing
2020-04-13 - WIP, DRU finished
2020-04-13 - Finishing up for quoting
2020-04-13 - Fixed via size to comply with drill level A
2020-04-13 - Raspberry extension
2020-04-13 - Added sample of opto-coupler
2020-04-13 Current sensor
2020-04-13 - Fixed solar TCP open/close loop - Added logs to listen socket issue on raspbian (missing POLLINVALID check?)
2020-04-18 - i18n in garden
2020-04-19 - Upgraded and fixed mcu card prod
2020-04-19 - Readded proto board settings - Fixed new project upgrade
2020-04-22 - Added suspended and reminder mail
2020-04-22 - Done
2020-04-27 - Added suspend/resume UI
2020-04-27 - WIP editor for cycles
2020-04-29 - Resume from rain now updates the start time
2020-04-29 - Hide Stop command if not running
2020-04-29 - Added login precheck
2020-04-29 - Fixed next cycle calculation after rain
2020-05-01 - Refactored zone names managements
2020-05-03 - Introduced optional sinks
2020-05-03 - Found issue in waiting the PL011 raspberrys to be clear sometimes
2020-05-07 - Fixed messy children registration in case of populated node startup
2020-05-07 - Send restart mail with exception stack
2020-05-08 - Fixed raspberry loop due to stale TCP connection: now keep-alive is set - Fixed issue in unzombie
2020-05-09 - Clean up and some doc
2020-05-10 - Fixed reset reason in microBean: software exception was reported as MCrl, causing zero-configuration address assignment - Using real pointers instead of BYTE used for older PIC models
2020-05-10 - Added a way to immediately re-fetch status in case of sub-node errors
2020-05-13 - Optimized check in case of node error notification - Added tester code to raise exception at timer
2020-05-13 - Fixed exception text in microbean
2021-01-06 - SAMIL: New error code witnessed
2021-05-22 - Support for 'broken' undocumented checksum?
2022-10-20 - Added scripts to aggregate yearly solar data
2022-10-20 - Switched to CMake
2022-10-20 - Silenced warnings
2022-10-23 - Splitting primary/secondary bus srcs
2022-10-25 - Migrated XC8 projects to C99
2022-10-25 - Migrated garden as well
2022-10-26 - Linted
2022-10-27 - Renamed inc to c
2022-10-29 - Better split between prim/sec and protocol
2022-10-29 - Alignment on PIC side
2022-10-29 linux to posix
2022-10-29 - Cleanup
2022-10-31 - WIP cmake lib
2022-11-01 - Sources and includes refactoring
2022-11-01 - Relocated headers
2022-11-02 - Posix target is building
2022-11-02 - Cleanup for last exception
2022-11-05 - Fixed build on eth card
2022-11-05 - Enabling all the sample sinks
2022-11-06 - Removed warnings
2022-11-06 - Fixed microbean
2022-11-06 - Moved away DEBUG
2023-05-14 - Migrated to lmartorella/pic-modbus
2023-05-14 - To test
2023-05-14 - Converted named pipe API to MQTT
2023-05-16 - Extracted devices to different transformer processes
2023-05-17 - Removed obsoleted sink simulators - Correct bootstrap info for all applications
2023-05-19 - Implemented solar protocol
2023-05-19 - Timeout and fixes
2023-05-20 Done flow and switch
2023-05-21 Migration to new API completed
2023-05-23 - ES module conversion - Fixed MQTT connection management
2023-05-23 Managed reconnections via ManagedClient
2023-05-26 - FIxed timeouts and protocol - Using managed client for persistent subscriptions
2023-05-28 - implemented logs
2023-05-28 - Fixed error management (500)
2023-05-28 - Fixed notification.json shared access - Fixed serialization types - Fixed exception if sink is down
2023-05-29 - Fixed support for disconnected flow sensor
2023-07-22 - Fixed exception in solar when offline
2023-08-01 - Adding partial results
2023-09-02 - Fixed protocol of reg 0x3
2023-09-02 - Some rev eng on Sofar
2023-09-02 - Missing timestamps
2023-09-02 WIP .NET poll code
    - Removed backups
2023-09-02 - WIP refactoring complete
2023-09-02 - String resources
2023-09-02 - Installed Angular 16
2023-09-02 - MIgrated garden
2023-09-03 - Migrated solar + plotly upgrade - Lazy load plotly
2023-09-03 - Added favicon - Fixed build warnings
2023-09-03 - FIxed security issue with secrets
2023-09-03 - Build/deploy optimization
2023-09-03 - Purged empty solar tests
2023-09-10 - Cleaning up files
2023-09-10 - Refolder solar
2023-09-10 - Moving sources
2023-09-10 - Using solar lib
2023-09-24 - Fixed deps and config API
2023-10-07 - Fixed process manager for .NET 7.0 project
2023-10-08 - Fixed restart pm
2023-10-11 - Angular CLI cache too much aggressive
2023-10-11 - Introduced metadata file for processes
2023-10-11 - Moved around
2023-10-11 - Simplified kill MQTT channel. - Using Ctrl-C event requires NAPI
2023-10-15 - Align subtree
2023-10-16 - Removed solar as submodule
2024-04-01 - Removing old net-related code
2024-04-01 - Boilerplate .NET Core 8
2024-04-01 - Adding IoC
2024-04-02 - Using MS structure
2024-04-03 - Added output switch logger
2024-04-07 - Restoring config
2024-04-09 - Get config and status done
2024-04-27 - Tested online status
2024-04-27 - Fixed loggers
2024-04-27 - New namespace style for .cs files
2024-04-27 - Status to RPC
2024-05-19 - Preparing config service
2024-05-19 - Added notification service
2024-05-19 - Mock to simulate switch change
2024-05-19 - Implemented activity notifier
2024-05-19 - FIxed hosted service singleton registration
2024-05-19 - Missing services
2024-05-19 - Working
2024-05-20 - Fixed package
2024-05-20 - Sending mail via MQTT
2024-06-09 - resx not supported
2024-06-09 - Support for post
2024-06-11 - Fixed error message in case of timeout
2024-06-11 - Fixed mqtt configured on IPV4 only
2024-06-11 - Completed editor
2024-06-11 - Console log in mock
2024-06-14 - Fixed multiple event changes
2024-06-15 - Removed dep to config for tests
2024-06-15 - Enabling italian by default
2024-06-16 - Added log timestamps
2024-06-17 - Fixed assembly name and target
2024-06-17 - Fixed assembly name
2024-06-17 - More logs
2024-06-19 - Removed unused field (liters)
2024-06-19 - Sending restart mail from process manager
2024-06-20 - Fixed target paths
2024-06-20 - Fixed unhandled exception mgmnt mqtt
2024-06-23 - Imported status enqueue logic from solar
2024-06-23 - Fixing config get/put
2024-06-23 - Not implemented
2024-06-23 - Fixed download/get
2024-06-24 - Log
2024-06-26 - Fixed mock and comment
2024-06-29 - Notification service now respond to RPC immediately rather than waiting for the mail to be sent
2024-07-11 - Enforced clean start and resubscribe after reconnection - Added more event logs
2024-07-11 - Changed namespace syntax
2024-07-13 - Added support for common mqttHost arg
2024-07-13 - Added WaitConnected
2024-07-16 - Version upgrade to leverage sub events
2024-07-17 - Enforced clean start and resubscribe after reconnection - Added more event logs - Aligned with net MqttService API
2024-07-17 Revert "- Enforced clean start and resubscribe after reconnection"
    This reverts commit d8df5346d6d0b45e9e55e7a1bbde1bf13faa629a.
2024-07-17 - Upgraded MQTTNet
2024-07-21 - MQTT debug level with --debug true switch
2024-07-24 - Moved target up
2024-07-24 - Merged folders
2024-07-27 - Re-merged web-server - Removed empty folders
    - Fixed mqtt in server
2024-07-27 - Remerged ui libs and C# src
2024-07-27 - Web-server in /target as well to ease the deploy
2024-07-27 - Re-merged solar ui lib in ui
2024-07-27 - Moved solar C# srcs
2024-07-27 - Split modbus bridge from main solar process
2024-07-27 - Removed custom wrk server's arg
2024-07-27 - Fail fast in MQTT handlers
2024-07-27 - Restored UT - Folder rename
2024-07-27 - Merged current sensor support in solar server
2024-07-27 - Renamed
2024-07-27 - Upgraded sample to pic-modbus lib
2024-07-27 - Preparing multi-channel support, modbus API side
2024-07-27 - Two analog channels, multiplexed
2024-07-27 - Fixed period sampling, independent on caller
2024-07-27 - Removed calibration, to move to a separate branch
2024-07-27 - Tested OK
2024-07-27 - Added power logger TCP modbus
2024-07-27 - Adapted new PIC module
2024-07-28 - Fixed exception - Removed workaround for FluentModbus MR
2024-07-28 - Dep upgrade
2024-07-28 - Re-added reminder e-mail
2024-07-28 - Removed not-implemented advanced UI
2024-07-28 - Removed dependency on msbuild
2024-07-28 - Fixed error reporting
2024-07-28 - Configuration working via RPC, mock used
2024-07-28 - Added exported current measurement to CSV, to run analysis and do calibration

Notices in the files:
garden/board_disp.brd:
(C)2016
mcu_board.brd:
LuxHardware (C)2016
